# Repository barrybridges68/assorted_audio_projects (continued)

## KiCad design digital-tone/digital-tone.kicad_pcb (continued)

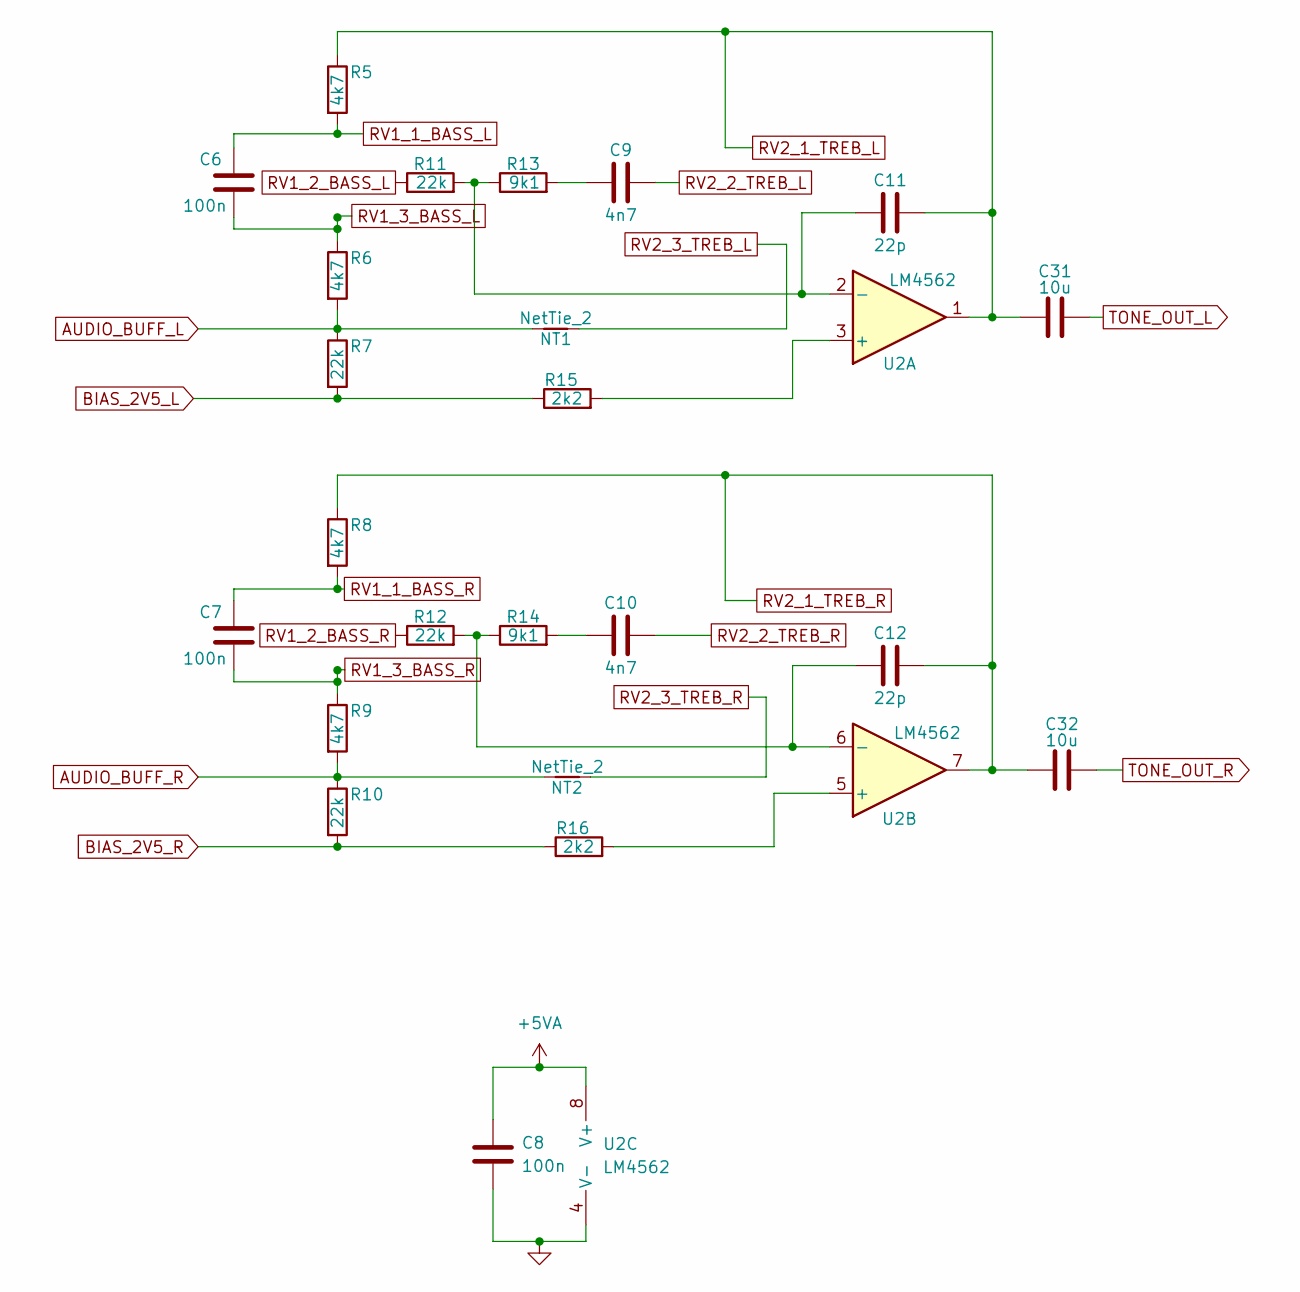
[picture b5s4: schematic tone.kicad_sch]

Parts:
C6, C7, C8: 100n; C_0603_1608Metric_Pad1.08x0.95mm_HandSolder
C9, C10: 4n7; C_0603_1608Metric_Pad1.08x0.95mm_HandSolder
C11, C12: 22p; C_0603_1608Metric_Pad1.08x0.95mm_HandSolder
C31, C32: 10u; C_1206_3216Metric
NT1, NT2: NetTie_2; NetTie-2_SMD_Pad0.5mm
R5, R6, R8, R9: 4k7; R_0603_1608Metric_Pad0.98x0.95mm_HandSolder
R7, R10, R11, R12: 22k; R_0603_1608Metric_Pad0.98x0.95mm_HandSolder
R13, R14: 9k1; R_0603_1608Metric_Pad0.98x0.95mm_HandSolder
R15, R16: 2k2; R_0603_1608Metric_Pad0.98x0.95mm_HandSolder
U2: LM4562; SOIC-8_3.9x4.9mm_P1.27mm

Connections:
+5VA: C8.1, U2.8 (V+); also elsewhere on the board
AUDIO_BUFF_L: NT1.1, R6.2, R7.1; also elsewhere on the board
AUDIO_BUFF_R: NT2.1, R9.2, R10.1; also elsewhere on the board
BIAS_2V5_L: R7.2, R15.1; also elsewhere on the board
BIAS_2V5_R: R10.2, R16.1; also elsewhere on the board
unnamed: C9.1, R13.2
unnamed: C10.1, R14.2
unnamed: C11.1, R11.2, R13.1, U2.2 (-)
unnamed: C12.1, R12.2, R14.1, U2.6 (-)
unnamed: R15.2, U2.3 (+)
unnamed: R16.2, U2.5 (+)
RV1_1_BASS_L: C6.2, R5.2; also elsewhere on the board
RV1_1_BASS_R: C7.2, R8.2; also elsewhere on the board
RV1_2_BASS_L: R11.1; also elsewhere on the board
RV1_2_BASS_R: R12.1; also elsewhere on the board
RV1_3_BASS_L: C6.1, R6.1; also elsewhere on the board
RV1_3_BASS_R: C7.1, R9.1; also elsewhere on the board
RV2_1_TREB_L: C11.2, C31.2, R5.1, U2.1; also elsewhere on the board
RV2_1_TREB_R: C12.2, C32.2, R8.1, U2.7; also elsewhere on the board
RV2_2_TREB_L: C9.2; also elsewhere on the board
RV2_2_TREB_R: C10.2; also elsewhere on the board
RV2_3_TREB_L: NT1.2; also elsewhere on the board
RV2_3_TREB_R: NT2.2; also elsewhere on the board
TONE_OUT_L: C31.1; also elsewhere on the board
TONE_OUT_R: C32.1; also elsewhere on the board

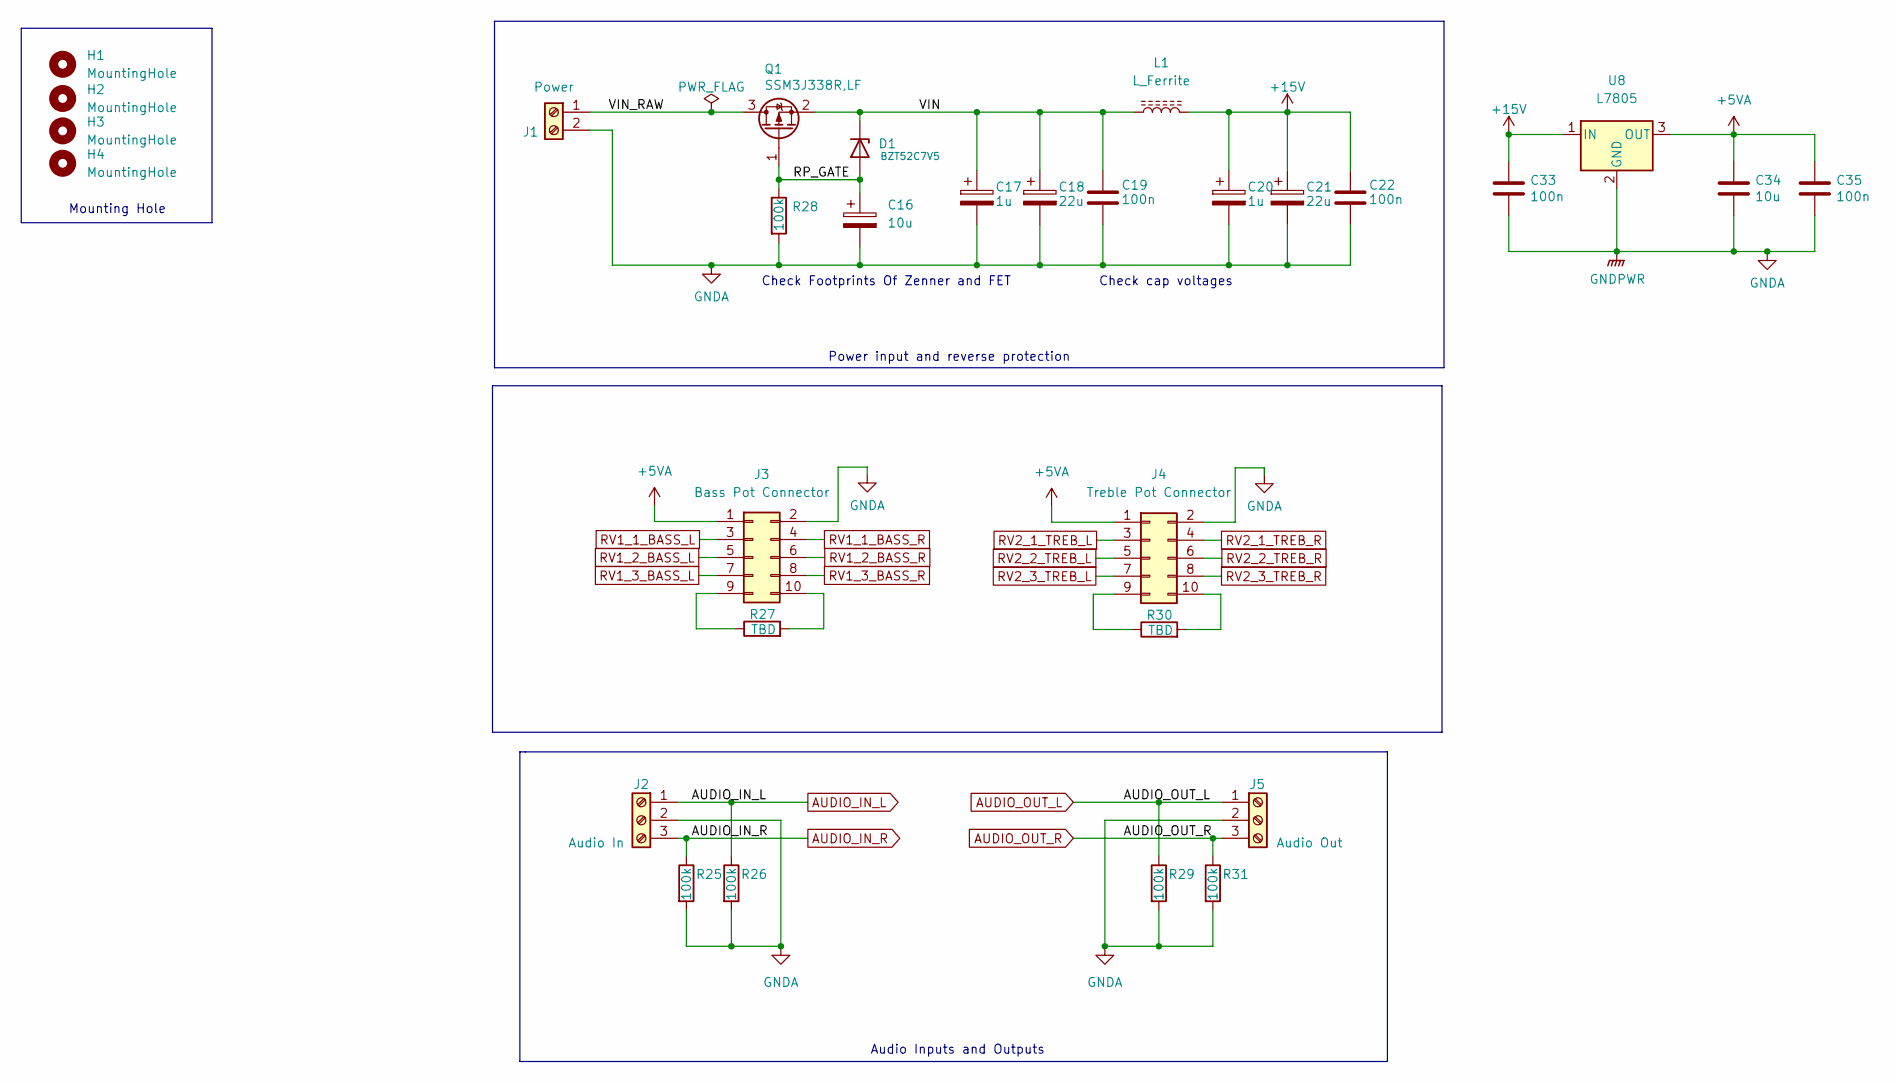
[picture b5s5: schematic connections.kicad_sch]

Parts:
C16: 10u; C_1206_3216Metric_Pad1.33x1.80mm_HandSolder
C17, C20: 1u; C_0603_1608Metric
C18, C21: 22u; CP_Elec_6.3x5.2
C19, C22, C33, C35: 100n; C_0603_1608Metric
C34: 10u; C_1206_3216Metric
D1: BZT52C7V5; D_SOD-123F
H1, H2, H3, H4: MountingHole; MountingHole_3.2mm_M3
J1: Power; TerminalBlock_Phoenix_MKDS-1,5-2_1x02_P5.00mm_Horizontal
J2: Audio In; TerminalBlock_Phoenix_MKDS-1,5-3_1x03_P5.00mm_Horizontal
J3: Bass Pot Connector; IDC-Header_2x05_P2.54mm_Vertical
J4: Treble Pot Connector; IDC-Header_2x05_P2.54mm_Vertical
J5: Audio Out; TerminalBlock_Phoenix_MKDS-1,5-3_1x03_P5.00mm_Horizontal
L1: L_Ferrite; R_0603_1608Metric
Q1: SSM3J338R,LF; SOT-23
R25, R26, R28, R29, R31: 100k; R_0603_1608Metric_Pad0.98x0.95mm_HandSolder
R27, R30: TBD; R_0603_1608Metric_Pad0.98x0.95mm_HandSolder
U8: L7805; TO-252-2

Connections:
+5VA: C34.1, C35.1, J3.1, J4.1, U8.3 (OUT); also elsewhere on the board
+15V: C20.1, C21.1, C22.1, C33.1, L1.2, U8.1 (IN); also elsewhere on the board
/connections/RP_GATE: C16.1, D1.2 (A), Q1.1 (G), R28.1
/connections/VIN: C17.1, C18.1, C19.1, D1.1 (K), L1.1, Q1.2 (S)
/connections/VIN_RAW: J1.1, Q1.3 (D)
AUDIO_IN_L: J2.1, R26.1; also elsewhere on the board
AUDIO_IN_R: J2.3, R25.1; also elsewhere on the board
AUDIO_OUT_L: J5.1, R29.1; also elsewhere on the board
AUDIO_OUT_R: J5.3, R31.1; also elsewhere on the board
unnamed: J3.9, R27.1
unnamed: J3.10, R27.2
unnamed: J4.9, R30.1
unnamed: J4.10, R30.2
RV1_1_BASS_L: J3.3; also elsewhere on the board
RV1_1_BASS_R: J3.4; also elsewhere on the board
RV1_2_BASS_L: J3.5; also elsewhere on the board
RV1_2_BASS_R: J3.6; also elsewhere on the board
RV1_3_BASS_L: J3.7; also elsewhere on the board
RV1_3_BASS_R: J3.8; also elsewhere on the board
RV2_1_TREB_L: J4.3; also elsewhere on the board
RV2_1_TREB_R: J4.4; also elsewhere on the board
RV2_2_TREB_L: J4.5; also elsewhere on the board
RV2_2_TREB_R: J4.6; also elsewhere on the board
RV2_3_TREB_L: J4.7; also elsewhere on the board
RV2_3_TREB_R: J4.8; also elsewhere on the board

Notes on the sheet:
Check cap voltages
Power input and reverse protection
Check Footprints Of Zenner and FET
Audio Inputs and Outputs
Mounting Hole

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
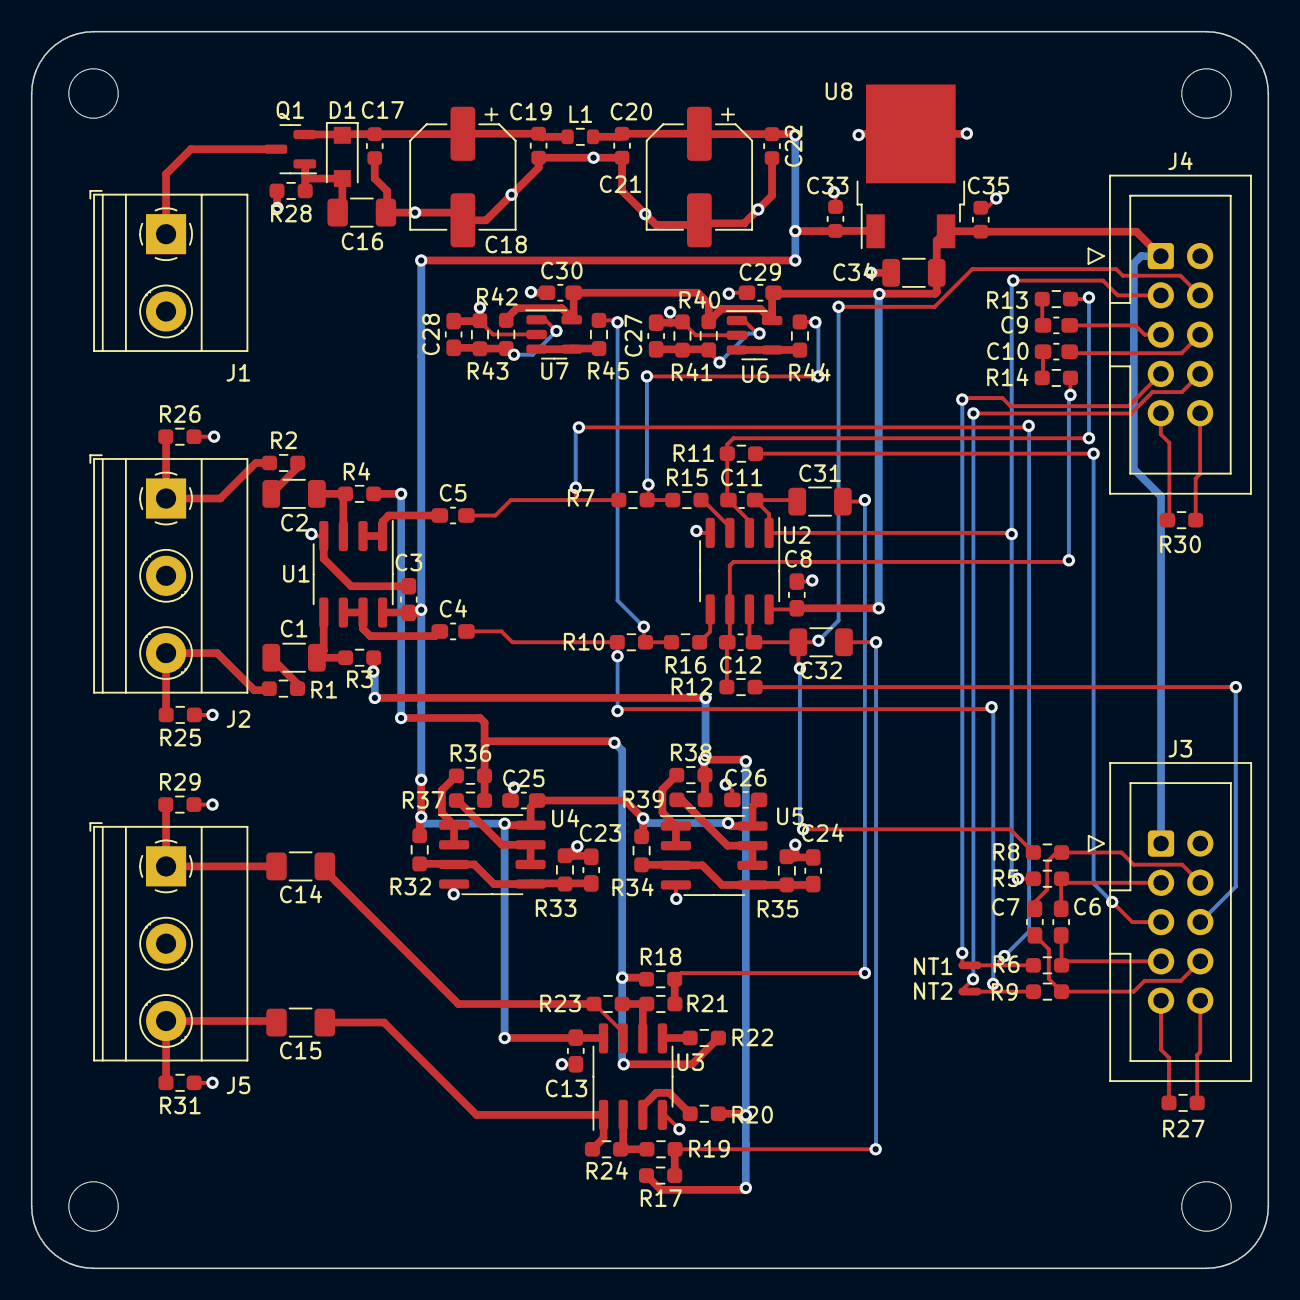
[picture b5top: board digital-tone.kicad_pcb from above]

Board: 2 copper layers, 80.0 x 80.0 mm, 102 parts (0 on the bottom side), 62 nets.

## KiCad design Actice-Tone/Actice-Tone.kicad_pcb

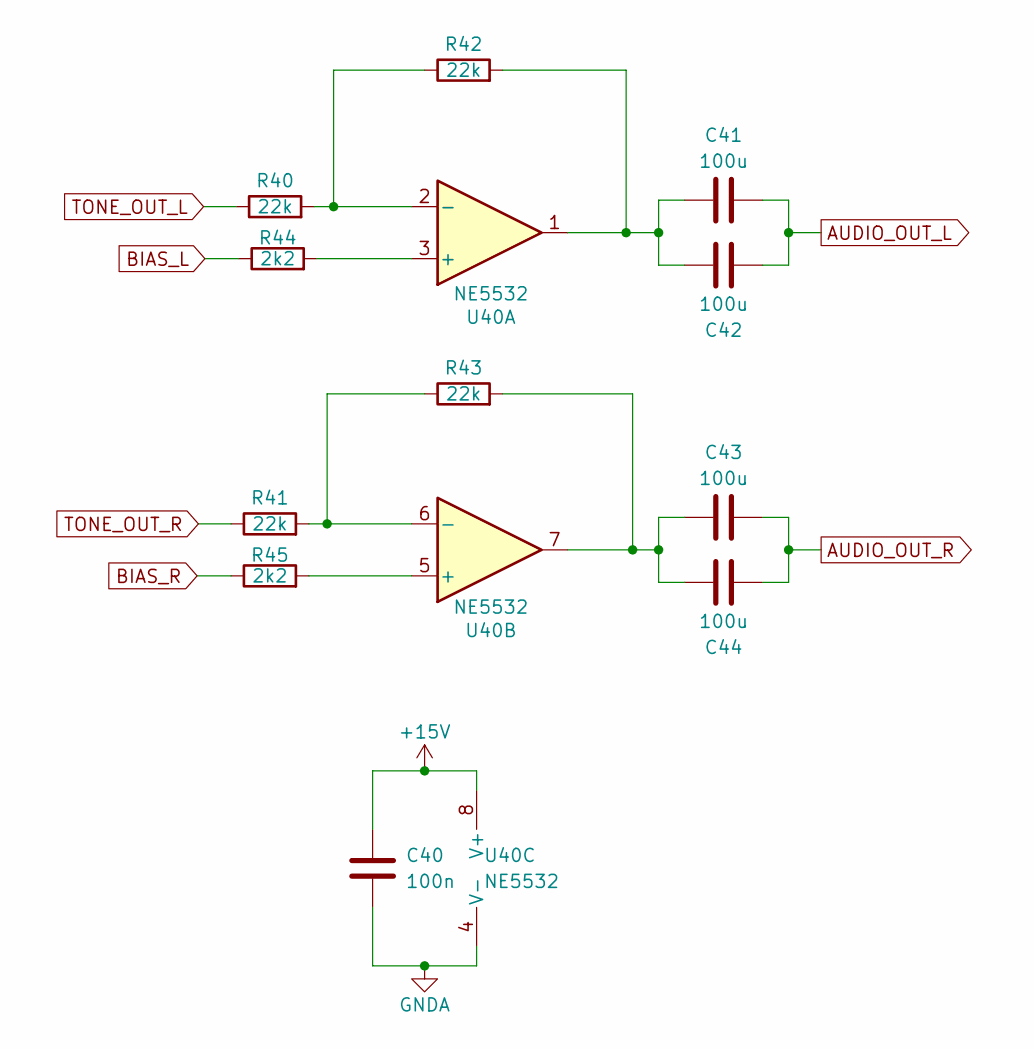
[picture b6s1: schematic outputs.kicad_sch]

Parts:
C40: 100n; C_0603_1608Metric_Pad1.08x0.95mm_HandSolder
C41, C42, C43, C44: 100u; C_1206_3216Metric_Pad1.33x1.80mm_HandSolder
R40, R41, R42, R43: 22k; R_0603_1608Metric_Pad0.98x0.95mm_HandSolder
R44, R45: 2k2; R_0603_1608Metric_Pad0.98x0.95mm_HandSolder
U40: NE5532; SOIC-8_3.9x4.9mm_P1.27mm

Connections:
AUDIO_OUT_L: C41.2, C42.1; also elsewhere on the board
AUDIO_OUT_R: C43.2, C44.1; also elsewhere on the board
BIAS_L: R44.1; also elsewhere on the board
BIAS_R: R45.1; also elsewhere on the board
unnamed: C41.1, C42.2, R42.2, U40.1
unnamed: C43.1, C44.2, R43.2, U40.7
unnamed: R40.2, R42.1, U40.2 (-)
unnamed: R41.2, R43.1, U40.6 (-)
unnamed: R44.2, U40.3 (+)
unnamed: R45.2, U40.5 (+)
TONE_OUT_L: R40.1; also elsewhere on the board
TONE_OUT_R: R41.1; also elsewhere on the board

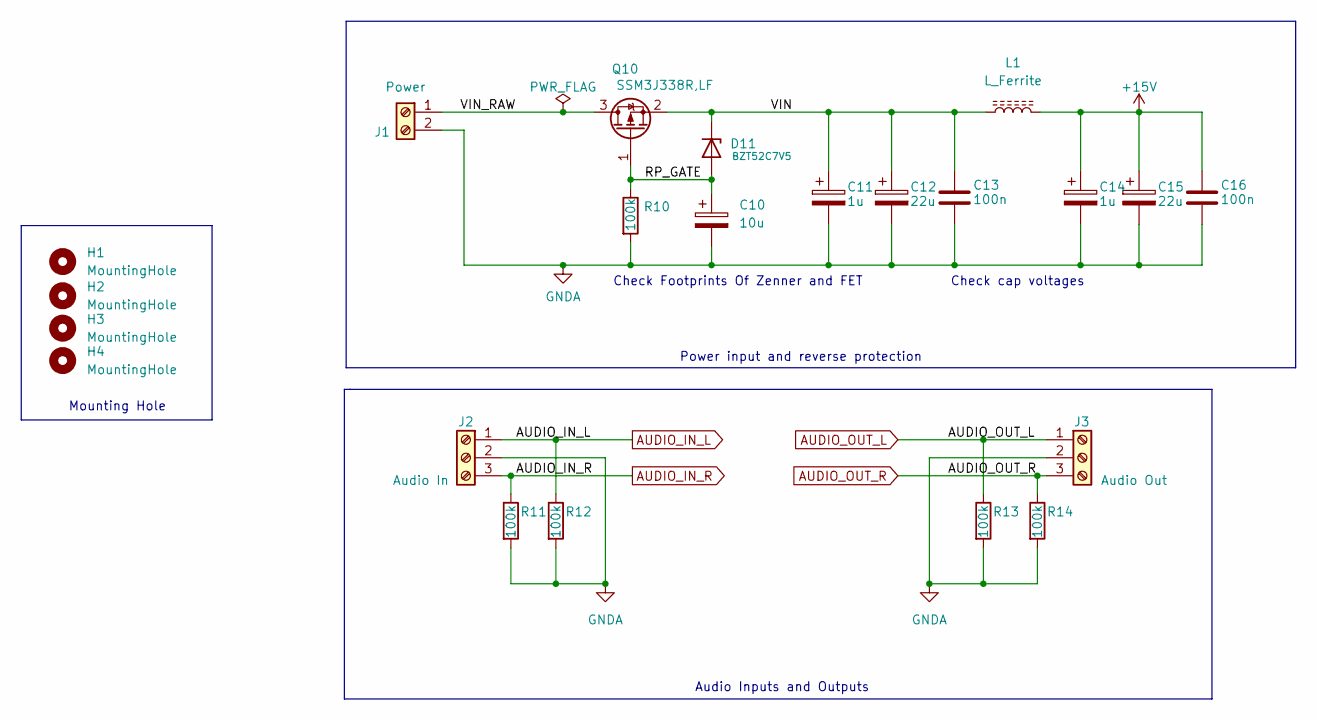
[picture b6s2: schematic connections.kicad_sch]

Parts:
C10: 10u; C_1206_3216Metric_Pad1.33x1.80mm_HandSolder
C11, C14: 1u; C_0603_1608Metric
C12, C15: 22u; CP_Elec_6.3x5.2
C13, C16: 100n; C_0603_1608Metric
D11: BZT52C7V5; D_SOD-123F
H1, H2, H3, H4: MountingHole; MountingHole_3.2mm_M3
J1: Power; TerminalBlock_Phoenix_MKDS-1,5-2_1x02_P5.00mm_Horizontal
J2: Audio In; TerminalBlock_Phoenix_MKDS-1,5-3_1x03_P5.00mm_Horizontal
J3: Audio Out; TerminalBlock_Phoenix_MKDS-1,5-3_1x03_P5.00mm_Horizontal
L1: L_Ferrite; R_0603_1608Metric
Q10: SSM3J338R,LF; SOT-23
R10, R11, R12, R13, R14: 100k; R_0603_1608Metric_Pad0.98x0.95mm_HandSolder

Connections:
/Connections/RP_GATE: C10.1, D11.2 (A), Q10.1 (G), R10.1
/Connections/VIN: C11.1, C12.1, C13.1, D11.1 (K), L1.1, Q10.2 (S)
/Connections/VIN_RAW: J1.1, Q10.3 (D)
AUDIO_IN_L: J2.1, R12.1; also elsewhere on the board
AUDIO_IN_R: J2.3, R11.1; also elsewhere on the board
AUDIO_OUT_L: J3.1, R13.1; also elsewhere on the board
AUDIO_OUT_R: J3.3, R14.1; also elsewhere on the board

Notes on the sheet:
Audio Inputs and Outputs
Check cap voltages
Power input and reverse protection
Mounting Hole
Check Footprints Of Zenner and FET

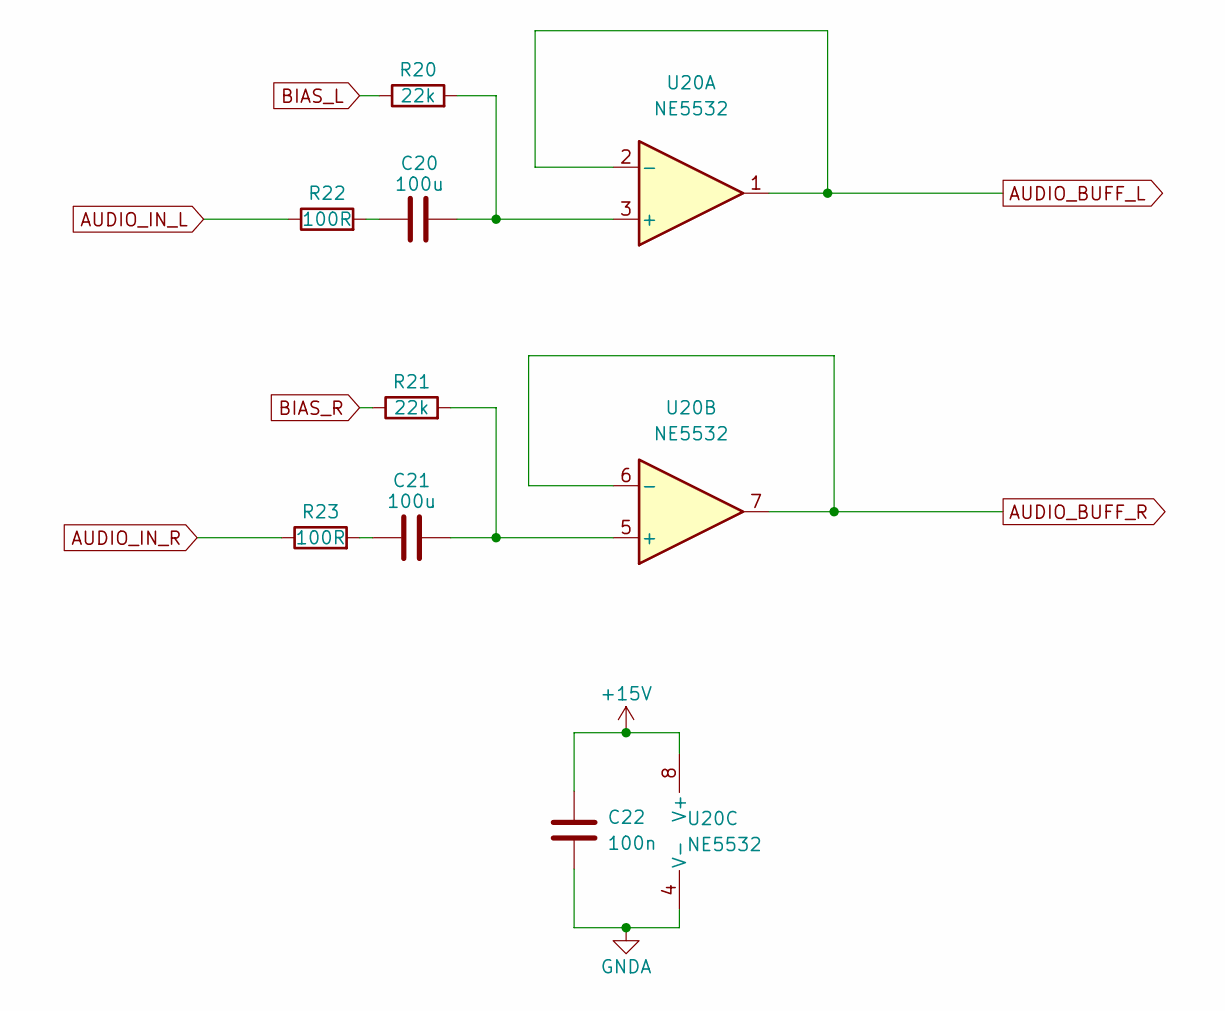
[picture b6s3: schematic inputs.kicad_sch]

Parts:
C20, C21: 100u; C_1206_3216Metric
C22: 100n; C_0603_1608Metric_Pad1.08x0.95mm_HandSolder
R20, R21: 22k; R_0603_1608Metric_Pad0.98x0.95mm_HandSolder
R22, R23: 100R; R_0603_1608Metric_Pad0.98x0.95mm_HandSolder
U20: NE5532; SOIC-8_3.9x4.9mm_P1.27mm

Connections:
AUDIO_BUFF_L: U20.1, U20.2 (-); also elsewhere on the board
AUDIO_BUFF_R: U20.6 (-), U20.7; also elsewhere on the board
AUDIO_IN_L: R22.1; also elsewhere on the board
AUDIO_IN_R: R23.1; also elsewhere on the board
BIAS_L: R20.1; also elsewhere on the board
BIAS_R: R21.1; also elsewhere on the board
unnamed: C20.1, R22.2
unnamed: C20.2, R20.2, U20.3 (+)
unnamed: C21.1, R23.2
unnamed: C21.2, R21.2, U20.5 (+)

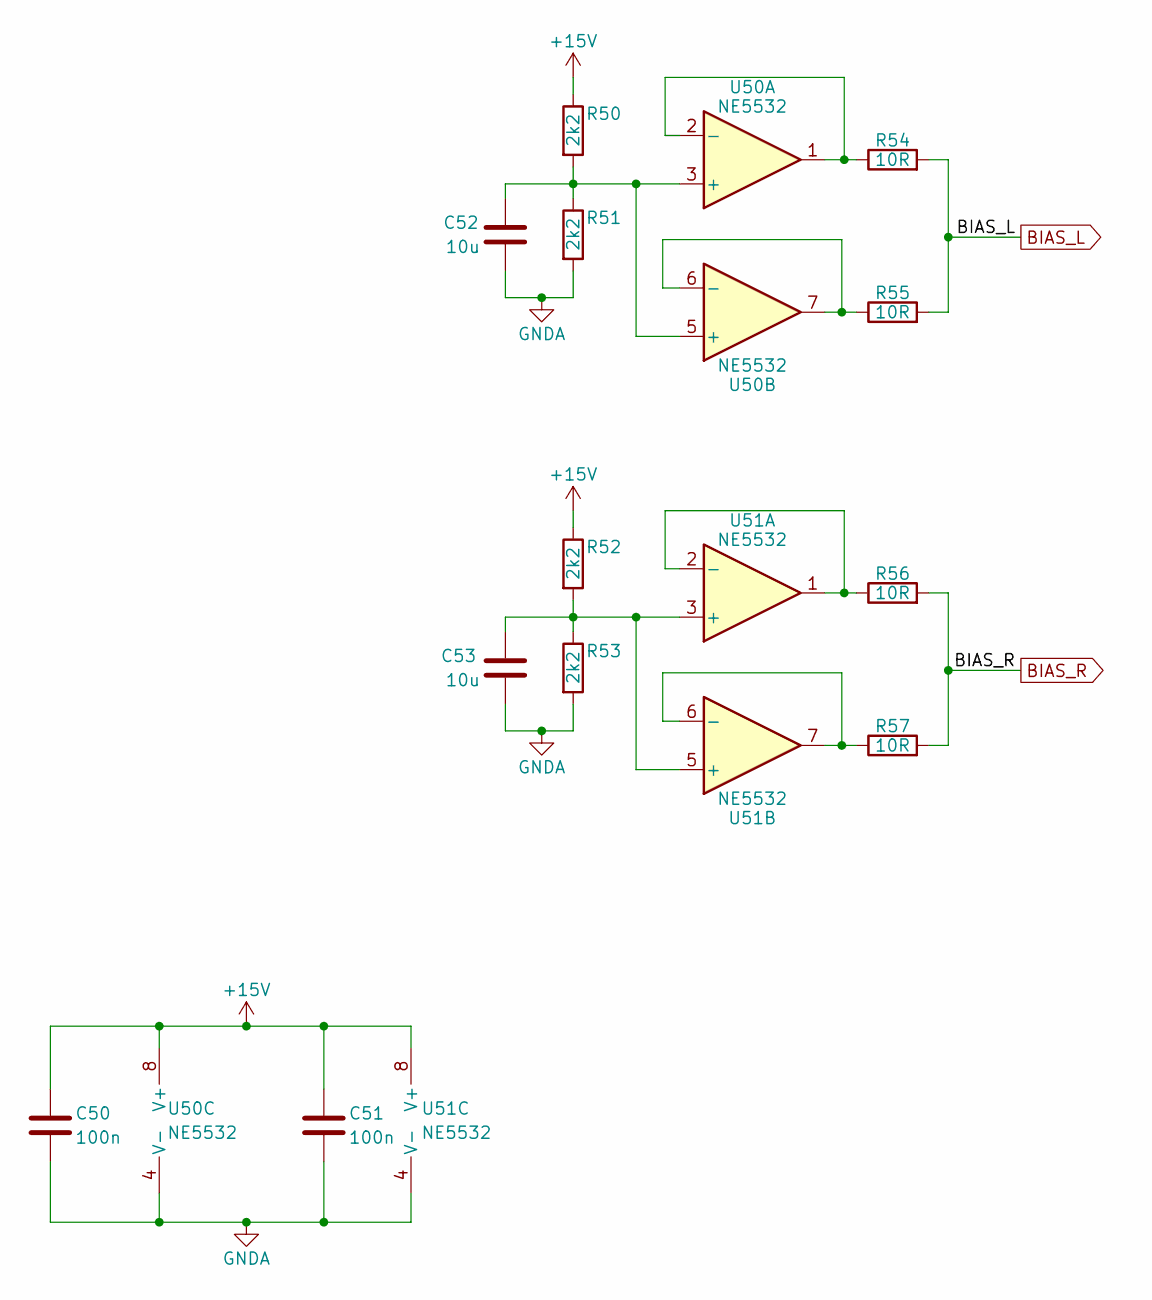
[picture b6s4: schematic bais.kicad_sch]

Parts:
C50, C51: 100n; C_0603_1608Metric_Pad1.08x0.95mm_HandSolder
C52, C53: 10u; C_0603_1608Metric_Pad1.08x0.95mm_HandSolder
R50, R51, R52, R53: 2k2; R_0603_1608Metric_Pad0.98x0.95mm_HandSolder
R54, R55, R56, R57: 10R; R_0603_1608Metric_Pad0.98x0.95mm_HandSolder
U50, U51: NE5532; SOIC-8_3.9x4.9mm_P1.27mm

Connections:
BIAS_L: R54.2, R55.2; also elsewhere on the board
BIAS_R: R56.2, R57.2; also elsewhere on the board
unnamed: C52.1, R50.2, R51.1, U50.3 (+), U50.5 (+)
unnamed: C53.1, R52.2, R53.1, U51.3 (+), U51.5 (+)
unnamed: R54.1, U50.1, U50.2 (-)
unnamed: R55.1, U50.6 (-), U50.7
unnamed: R56.1, U51.1, U51.2 (-)
unnamed: R57.1, U51.6 (-), U51.7

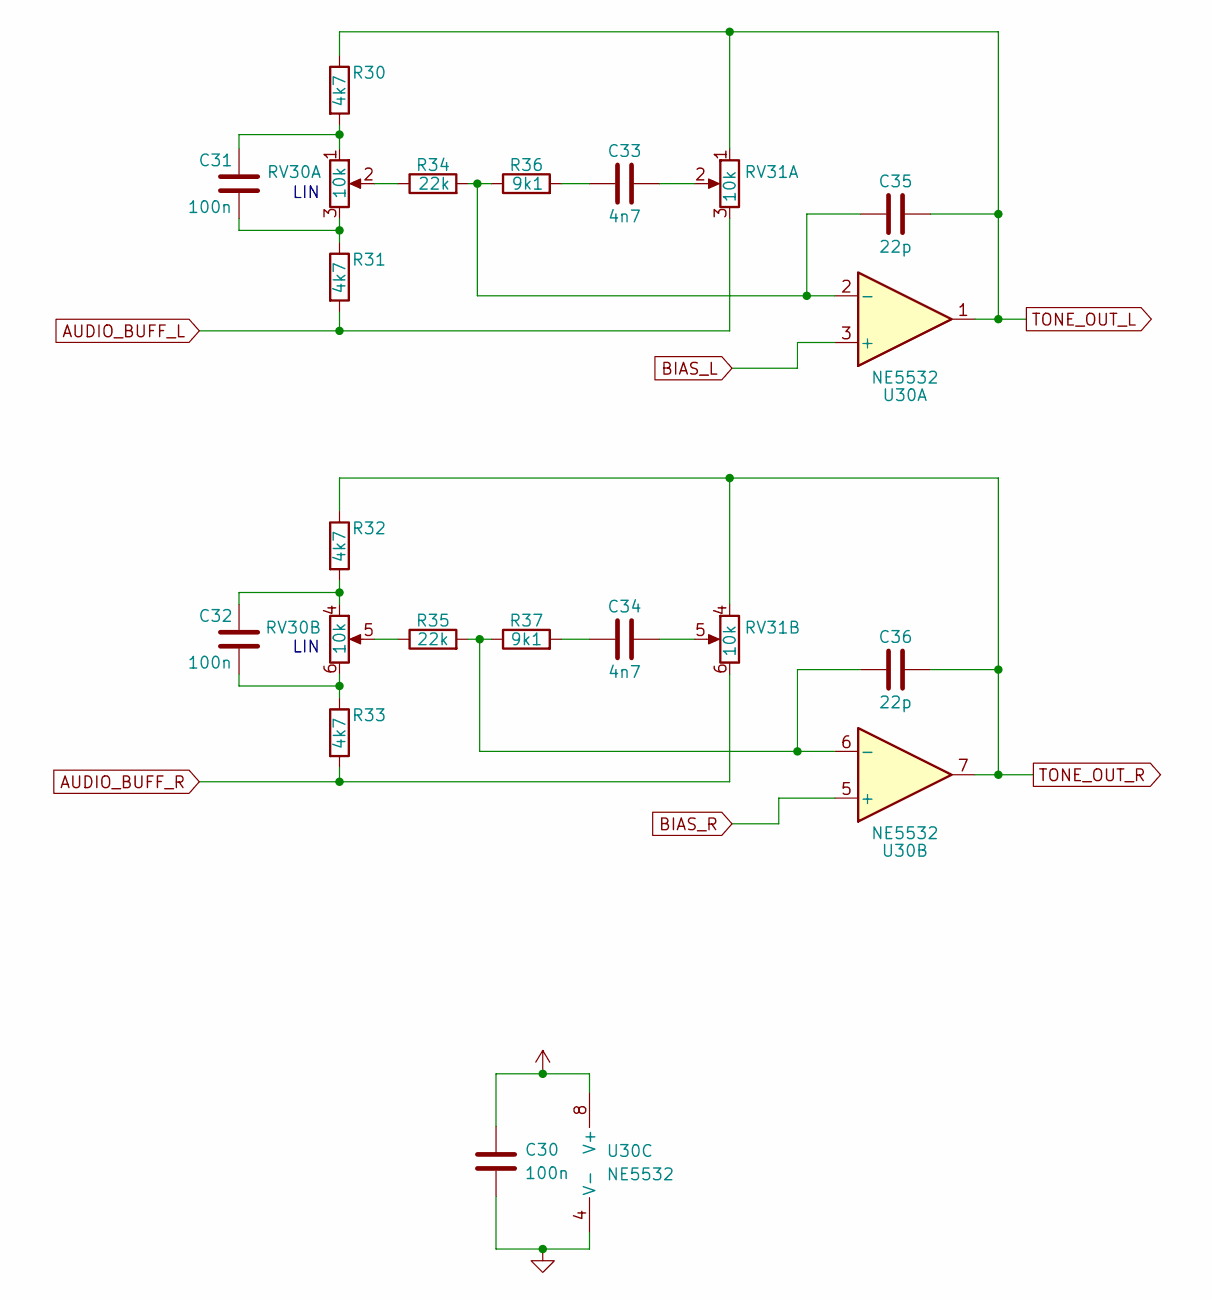
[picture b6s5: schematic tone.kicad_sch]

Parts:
C30, C31, C32: 100n; C_0603_1608Metric_Pad1.08x0.95mm_HandSolder
C33, C34: 4n7; C_0603_1608Metric_Pad1.08x0.95mm_HandSolder
C35, C36: 22p; C_0603_1608Metric_Pad1.08x0.95mm_HandSolder
R30, R31, R32, R33: 4k7; R_0603_1608Metric_Pad0.98x0.95mm_HandSolder
R34, R35: 22k; R_0603_1608Metric_Pad0.98x0.95mm_HandSolder
R36, R37: 9k1; R_0603_1608Metric_Pad0.98x0.95mm_HandSolder
RV30, RV31: 10k; Potentiometer_Alps_RK163_Dual_Horizontal
U30: NE5532; SOIC-8_3.9x4.9mm_P1.27mm

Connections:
AUDIO_BUFF_L: R31.2, RV31.3; also elsewhere on the board
AUDIO_BUFF_R: R33.2, RV31.6; also elsewhere on the board
BIAS_L: U30.3 (+); also elsewhere on the board
BIAS_R: U30.5 (+); also elsewhere on the board
unnamed: C31.1, R31.1, RV30.3
unnamed: C31.2, R30.2, RV30.1
unnamed: C32.1, R33.1, RV30.6
unnamed: C32.2, R32.2, RV30.4
unnamed: C33.1, R36.2
unnamed: C33.2, RV31.2
unnamed: C34.1, R37.2
unnamed: C34.2, RV31.5
unnamed: C35.1, R34.2, R36.1, U30.2 (-)
unnamed: C36.1, R35.2, R37.1, U30.6 (-)
unnamed: R34.1, RV30.2
unnamed: R35.1, RV30.5
TONE_OUT_L: C35.2, R30.1, RV31.1, U30.1; also elsewhere on the board
TONE_OUT_R: C36.2, R32.1, RV31.4, U30.7; also elsewhere on the board

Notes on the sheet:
LIN

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
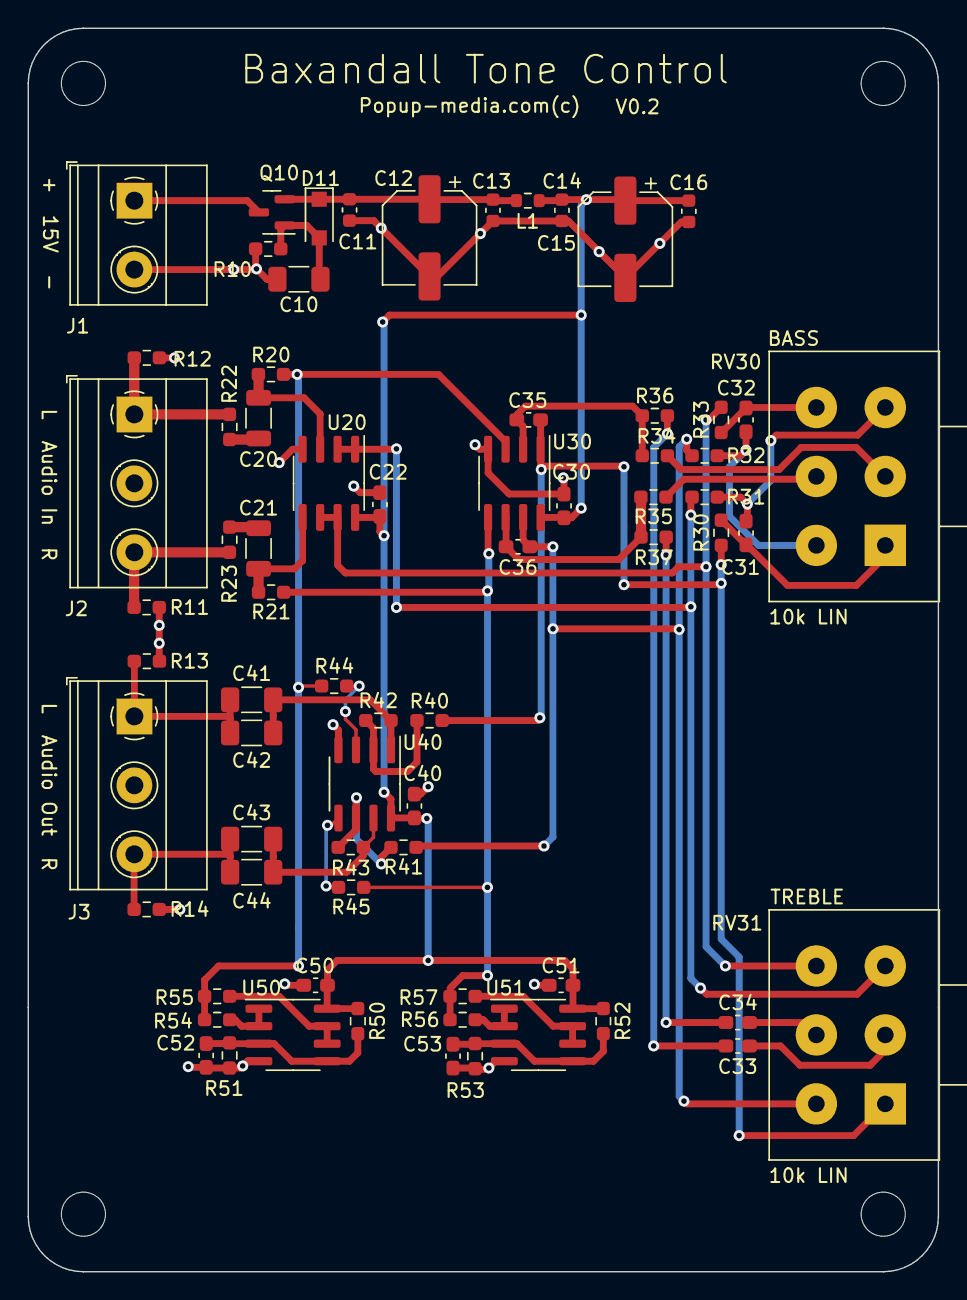
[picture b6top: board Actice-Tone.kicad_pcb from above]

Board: 2 copper layers, 66.0 x 90.2 mm, 74 parts (0 on the bottom side), 43 nets.

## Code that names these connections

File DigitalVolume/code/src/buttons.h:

#ifndef __BUTTONS_H__
#define __BUTTONS_H__

#define BTN_UP          P10
#define BTN_DWN         P11
#define BTN_MUTE        P12
#define BTN_PWR



void buttons_setup( void );
void wait_buttons_release( void );
uint8_t buttons_check( void );

#endif

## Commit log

2026-01-04 Commit of audio projects
2026-01-04 Add digital volume circuit
